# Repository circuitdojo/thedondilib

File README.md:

# The Dondi Lib

Part nightlight, part art, part Internet of Things. This little bluetooth enabled box will surprise and delight. For more info go [here](https://www.hackster.io/jaredwolff/the-dondi-lib-a-bluetooth-low-energy-light-box-cc7d90).

## Version One

### Features

1. Bluetooth Low Energy with a Rigado BMD-300 (nRF52832)
1. Lithium Battery support
1. Motion support
1. PIR Amplifier (Motion)
1. External connections for button, DC power, battery and PIR
1. Tag-Connect SWD connection

### Rework

Please note that this is Version 1 of the board. There are several (reworkable) issues with this board. 

1. U7A.1 should be connected to D9.C
1. D4.2 should be connected to VDC
1. J2.1 missing connection to VSYS
1. U2 changed to a LED1642GW
1. Untuffed U6 to accomodate LED driver above
1. LED_OE (PWM_CLK) connected to LIS2DH_INT

### License

Released under the Creative Commons Attribution-NonCommercial-NoDerivatives 4.0 International Public License. More info [here](https://creativecommons.org/licenses/by-nc-nd/4.0/legalcode).

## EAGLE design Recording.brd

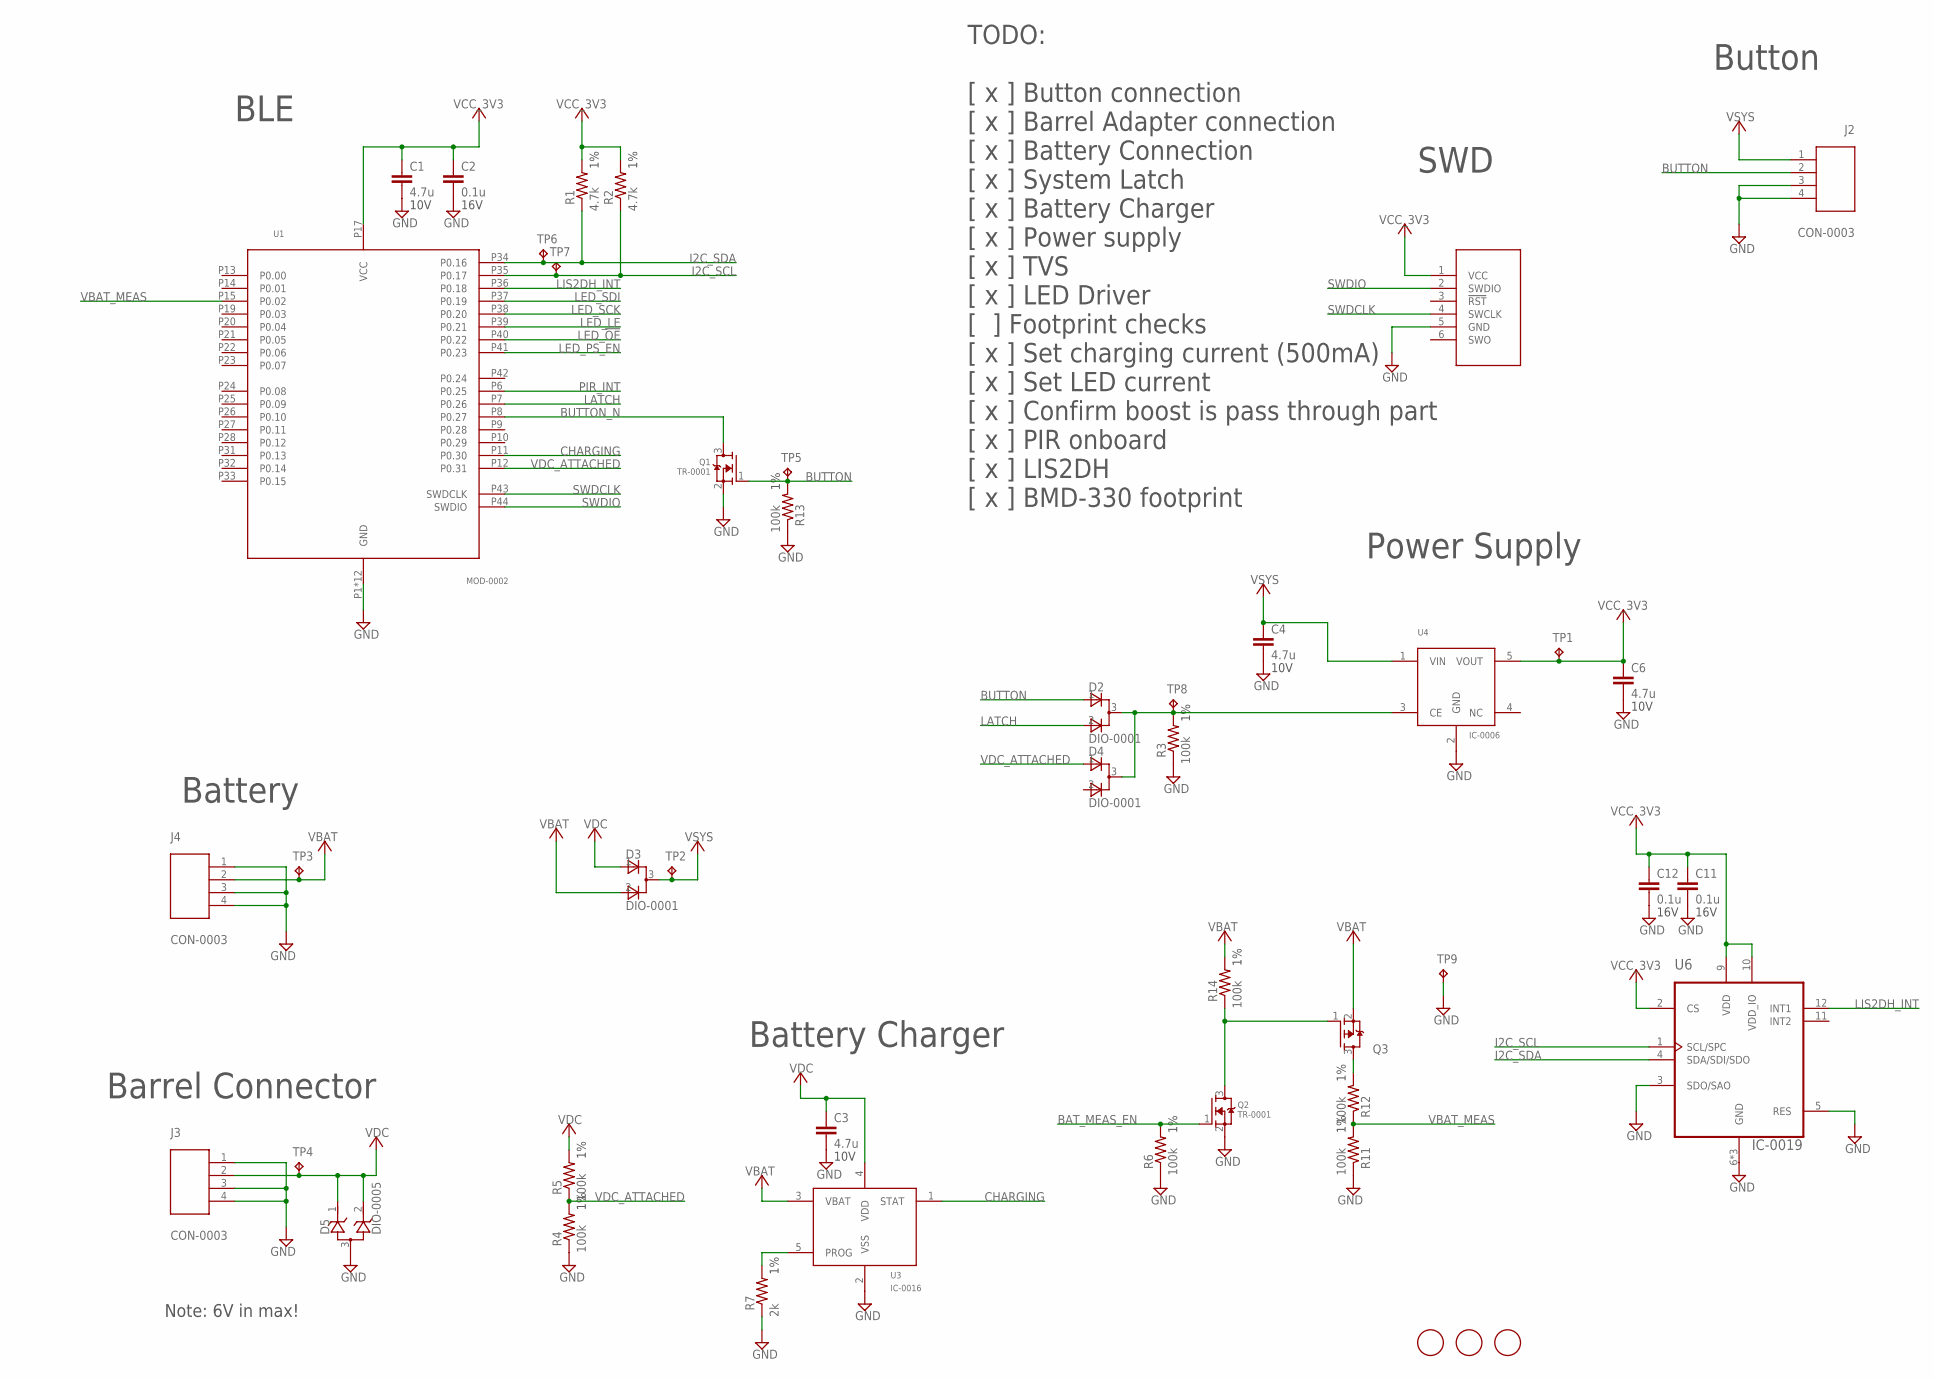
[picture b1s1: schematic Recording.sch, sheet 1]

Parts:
C1, C3, C4, C6: 4.7u; C0603
C2, C11, C12: 0.1u; C0603
D2, D3, D4: DIO-0001; SOT23
D5: DIO-0005; SOT23
J1: CON-0002; TC2030-MCP-NL
J2, J3, J4: CON-0003; CON-SM02B-SRSS-TB(LF)(SN)
Q1, Q2: TR-0001; SOT23
Q3: TR-0003; SOT23
R1, R2: 4.7k; R0603
R3, R4, R5, R6, R11, R12, R13, R14: 100k; R0603
R7: 2k; R0603
TP1, TP2, TP3, TP4, TP5, TP6, TP7, TP8, TP9: TP-0001; TP-1P27
U1: MOD-0002; MODULE-BMD-300
U3: IC-0016; SOT23-5
U4: IC-0006; SOT23-5
U6: IC-0019; PQFN50P200X200100-12N
U$1, U$2, U$3: FIDUCIAL; FIDUCIAL_1MM

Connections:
BAT_MEAS_EN: Q2.1 (G), R6.2
BAT_MEAS_P_GATE: Q2.3 (D), Q3.1 (G), R14.1
BUTTON: D2.1 (A1), J2.2, Q1.1 (G), R13.2, TP5.P$1, TP5.P$2, TP5.TP
BUTTON_N: Q1.3 (D), U1.P8 (P0.27)
CHARGER_PROG: R7.2, U3.5 (PROG)
CHARGING: U1.P11 (P0.30), U3.1 (STAT)
GND: C1.2, C2.2, C3.2, C4.2, C6.2, C11.2, C12.2, D5.3 (A), J1.5 (GND), J2.3, J2.4, J3.1, J3.3, J3.4, J4.1, J4.3, J4.4, Q1.2 (S), Q2.2 (S), R3.1, R4.1, R6.1, R7.1, R11.1, R13.1, TP9.P$1, TP9.P$2, TP9.TP, U1.P1 (GND), U1.P2 (GND), U1.P3 (GND), U1.P4 (GND), U1.P5 (GND), U1.P16 (GND), U1.P18 (GND), U1.P29 (GND), U1.P30 (GND), U1.P45 (GND), U1.P46 (GND), U1.P47 (GND), U3.2 (VSS), U4.2 (GND), U6.3 (SDO/SAO), U6.5 (RES), U6.6 (GND), U6.7 (GND), U6.8 (GND); also elsewhere on the board
I2C_SCL: R2.1, TP7.P$1, TP7.P$2, TP7.TP, U1.P35 (P0.17), U6.1 (SCL/SPC)
I2C_SDA: R1.1, TP6.P$1, TP6.P$2, TP6.TP, U1.P34 (P0.16), U6.4 (SDA/SDI/SDO)
LATCH: D2.2 (A2), U1.P7 (P0.26)
LED_!OE: U1.P40 (P0.22); also elsewhere on the board
LED_LE: U1.P39 (P0.21); also elsewhere on the board
LED_PS_EN: U1.P41 (P0.23); also elsewhere on the board
LED_SCK: U1.P38 (P0.20); also elsewhere on the board
LED_SDI: U1.P37 (P0.19); also elsewhere on the board
LIS2DH_INT: U1.P36 (P0.18), U6.12 (INT1)
PIR_INT: U1.P6 (P0.25); also elsewhere on the board
SWDCLK: J1.4 (SWCLK), U1.P43 (SWDCLK)
SWDIO: J1.2 (SWDIO), U1.P44 (SWDIO)
VBAT: D3.2 (A2), J4.2, Q3.2 (S), R14.2, TP3.P$1, TP3.P$2, TP3.TP, U3.3 (VBAT)
VBAT_MEAS: R11.2, R12.1, U1.P15 (P0.02)
VBAT_SW: Q3.3 (D), R12.2
VCC_3V3: C1.1, C2.1, C6.1, C11.1, C12.1, J1.1 (VCC), R1.2, R2.2, TP1.P$1, TP1.P$2, TP1.TP, U1.P17 (VCC), U4.5 (VOUT), U6.2 (CS), U6.9 (VDD), U6.10 (VDD_IO); also elsewhere on the board
VCC_3V3_EN: D2.3 (C), D4.3 (C), R3.2, TP8.P$1, TP8.P$2, TP8.TP, U4.3 (CE)
VDC: C3.1, D3.1 (A1), D5.1 (C1), D5.2 (C2), J3.2, R5.2, TP4.P$1, TP4.P$2, TP4.TP, U3.4 (VDD)
VDC_ATTACHED: D4.1 (A1), R4.2, R5.1, U1.P12 (P0.31)
VSYS: C4.1, D3.3 (C), TP2.P$1, TP2.P$2, TP2.TP, U4.1 (VIN); also elsewhere on the board

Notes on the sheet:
TODO: [ x ] Button connection [ x ] Barrel Adapter connection [ x ] Battery Connection [ x ] System Latch [ x ] Battery Charger [ x ] Power supply [ x ] TVS [ x ] LED Driver [ ] Footprint checks [ x ] Set charging current (500mA) [ x ] Set LED current [ x ] Confirm boost is pass through part [ x ] 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
Button
SWD
BLE
Battery
Barrel Connector
Note: 6V in max!
Battery Charger
Power Supply

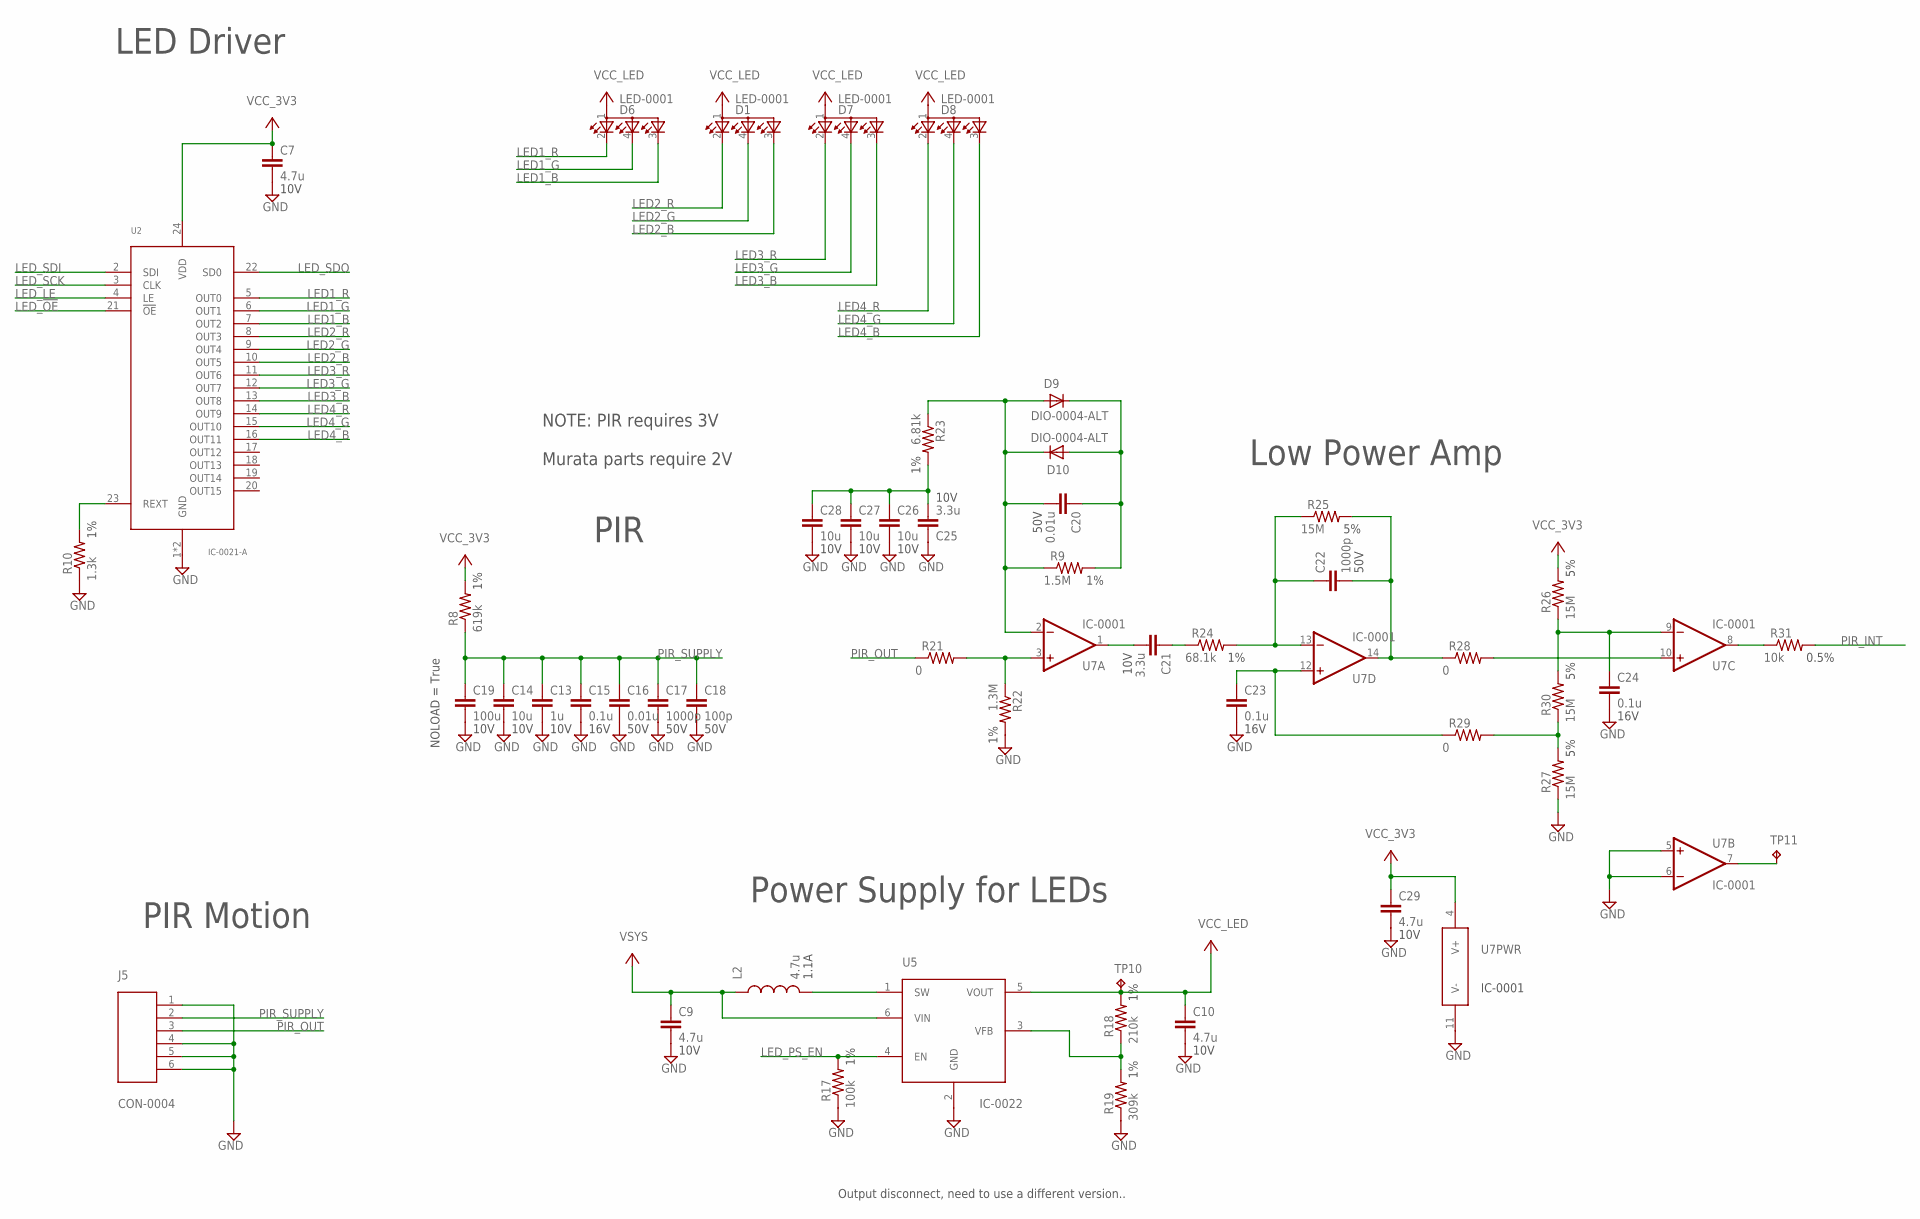
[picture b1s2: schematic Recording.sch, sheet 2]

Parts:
C7, C9, C10, C29: 4.7u; C0603
C13: 1u; C0603
C14, C26, C27, C28: 10u; C0805
C15, C23, C24: 0.1u; C0603
C16, C20: 0.01u; C0603
C17, C22: 1000p; C0603
C18: 100p; C0603
C19: 100u; C1210
C21, C25: 3.3u; C0603
D1, D6, D7, D8: LED-0001; LED_ASMB-KTF0-0A306
D9, D10: DIO-0004-ALT; SOD523
J5: CON-0004; CON-SM04B-SRSS-TB(LF)(SN)
L2: 4.7u; IND-2P0X2P0X1P2
R8: 619k; R0603
R9: 1.5M; R0603
R10: 1.3k; R0603
R17: 100k; R0603
R18: 210k; R0603
R19: 309k; R0603
R21, R28, R29: 0; R0603
R22: 1.3M; R0603
R23: 6.81k; R0603
R24: 68.1k; R0603
R25, R26, R27, R30: 15M; R0603
R31: 10k; R0603
TP10, TP11: TP-0001; TP-1P27
U2: IC-0021-A; SOP65P640X120-25N
U5: IC-0022; SOT23-6
U7: IC-0001; TSSOP14

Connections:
BOOST_FB: R18.1, R19.2, U5.3 (VFB)
BOOST_SW: L2.P$2 (2), U5.1 (SW)
GND: C7.2, C9.2, C10.2, C13.2, C14.2, C15.2, C16.2, C17.2, C18.2, C19.2, C23.2, C24.2, C25.1, C26.2, C27.2, C28.2, C29.2, J5.1, J5.4, J5.5, J5.6, R10.1, R17.1, R19.1, R22.2, R27.1, U2.1 (GND), U2.25 (GND), U5.2 (GND), U7.5 (+IN), U7.6 (-IN), U7.11 (V-); also elsewhere on the board
LED1_B: D6.3 (CGREEN), U2.7 (OUT2)
LED1_G: D6.4 (CBLUE), U2.6 (OUT1)
LED1_R: D6.2 (CRED), U2.5 (OUT0)
LED2_B: D1.3 (CGREEN), U2.10 (OUT5)
LED2_G: D1.4 (CBLUE), U2.9 (OUT4)
LED2_R: D1.2 (CRED), U2.8 (OUT3)
LED3_B: D7.3 (CGREEN), U2.13 (OUT8)
LED3_G: D7.4 (CBLUE), U2.12 (OUT7)
LED3_R: D7.2 (CRED), U2.11 (OUT6)
LED4_B: D8.3 (CGREEN), U2.16 (OUT11)
LED4_G: D8.4 (CBLUE), U2.15 (OUT10)
LED4_R: D8.2 (CRED), U2.14 (OUT9)
LED_!OE: U2.21 (!OE); also elsewhere on the board
LED_LE: U2.4 (LE); also elsewhere on the board
LED_PS_EN: R17.2, U5.4 (EN); also elsewhere on the board
LED_REXT: R10.2, U2.23 (REXT)
LED_SCK: U2.3 (CLK); also elsewhere on the board
LED_SDI: U2.2 (SDI); also elsewhere on the board
LED_SDO: U2.22 (SD0)
unnamed: C20.2, D9.A, D10.C, R9.1, R23.1, U7.2 (-IN)
unnamed: TP11.P$1, TP11.P$2, TP11.TP, U7.7 (OUT)
unnamed: C20.1, D9.C, D10.A, R9.2
unnamed: R21.2, R22.1, U7.3 (+IN)
unnamed: C25.2, C26.1, C27.1, C28.1, R23.2
unnamed: C21.2, U7.1 (OUT)
unnamed: C21.1, R24.1
unnamed: C22.1, R24.2, R25.1, U7.13 (-IN)
unnamed: C22.2, R25.2, R28.1, U7.14 (OUT)
unnamed: C23.1, R29.1, U7.12 (+IN)
unnamed: R28.2, U7.10 (+IN)
unnamed: R27.2, R29.2, R30.1
unnamed: C24.1, R26.1, R30.2, U7.9 (-IN)
PIR_INT: R31.2; also elsewhere on the board
PIR_INT_CL: R31.1, U7.8 (OUT)
PIR_OUT: J5.3, R21.1
PIR_SUPPLY: C13.1, C14.1, C15.1, C16.1, C17.1, C18.1, C19.1, J5.2, R8.1
VCC_3V3: C7.1, C29.1, R8.2, R26.2, U2.24 (VDD), U7.4 (V+); also elsewhere on the board
VCC_LED: C10.1, D1.1 (A2), D6.1 (A2), D7.1 (A2), D8.1 (A2), R18.2, TP10.P$1, TP10.P$2, TP10.TP, U5.5 (VOUT)
VSYS: C9.1, L2.P$1 (1), U5.6 (VIN); also elsewhere on the board

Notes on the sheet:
PIR Motion
Power Supply for LEDs
LED Driver
PIR
Low Power Amp
NOTE: PIR requires 3V Murata parts require 2V
Output disconnect, need to use a different version..

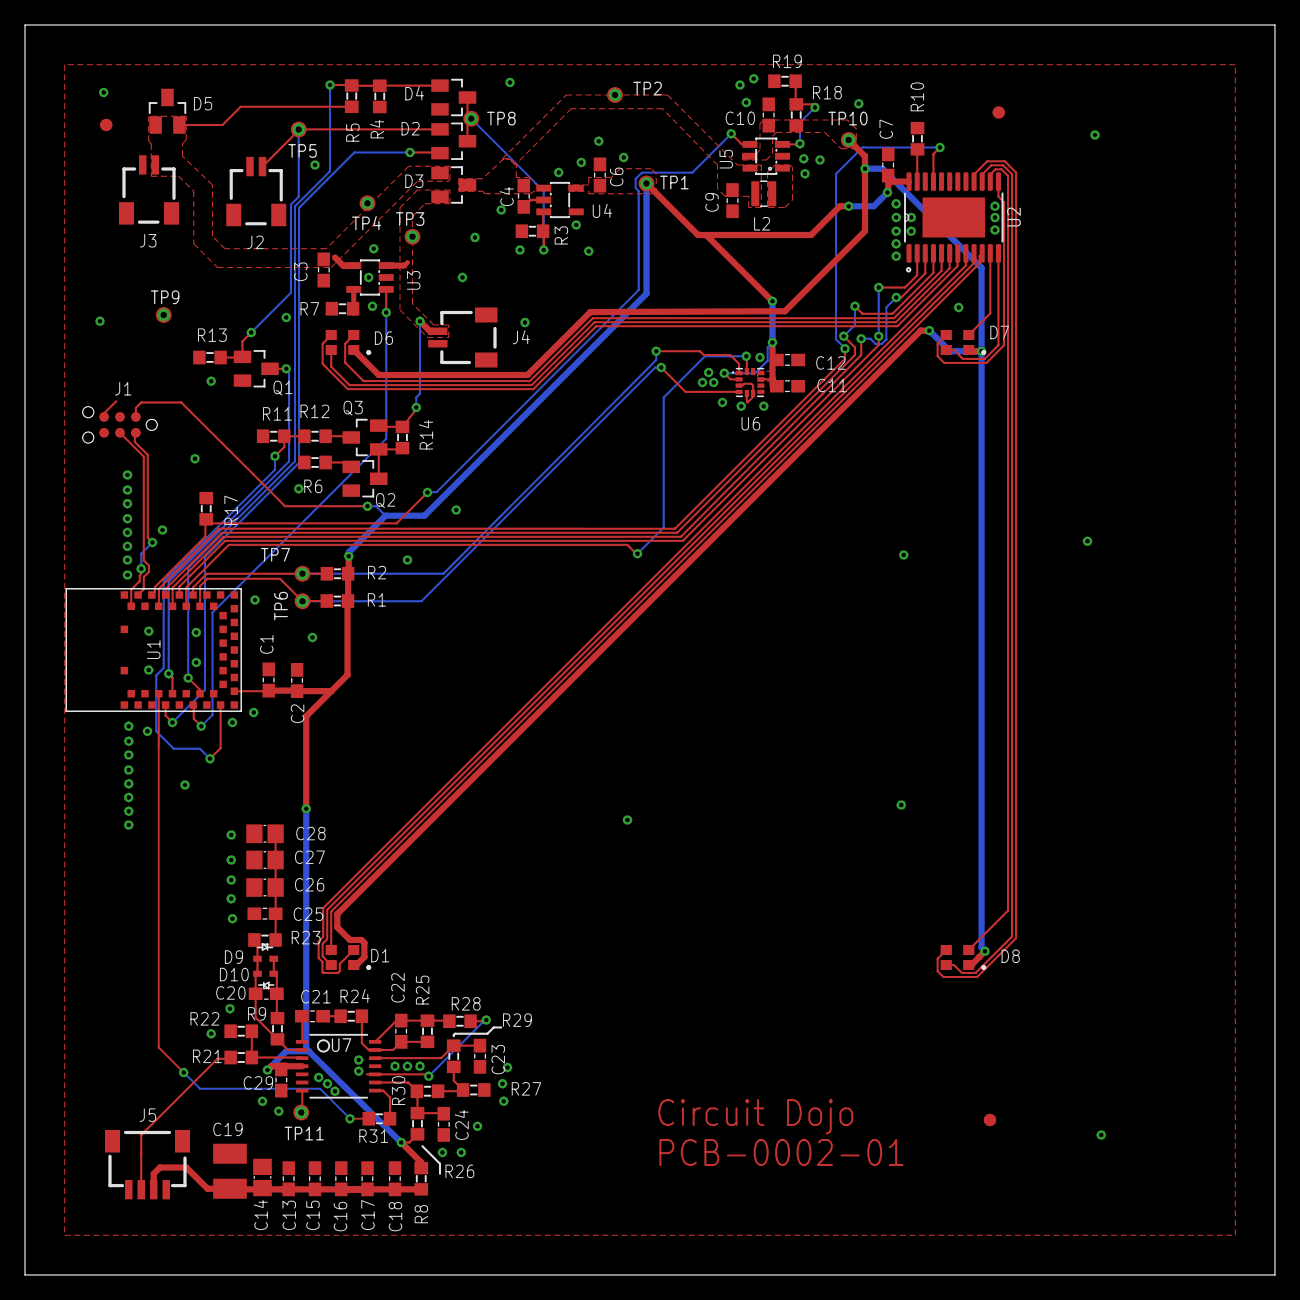
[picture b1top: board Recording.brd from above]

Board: 2 copper layers, 100.0 x 100.0 mm, 95 parts (0 on the bottom side), 59 nets.

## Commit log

2018-08-19 First commit of 1.0
2018-09-10 Update README.md
    Added license

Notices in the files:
parts and their libraries:
wolff-den: ©2009 ROFA.cz - modified and updated by Robert Darlington ‹rdarlington@gmail.com›
